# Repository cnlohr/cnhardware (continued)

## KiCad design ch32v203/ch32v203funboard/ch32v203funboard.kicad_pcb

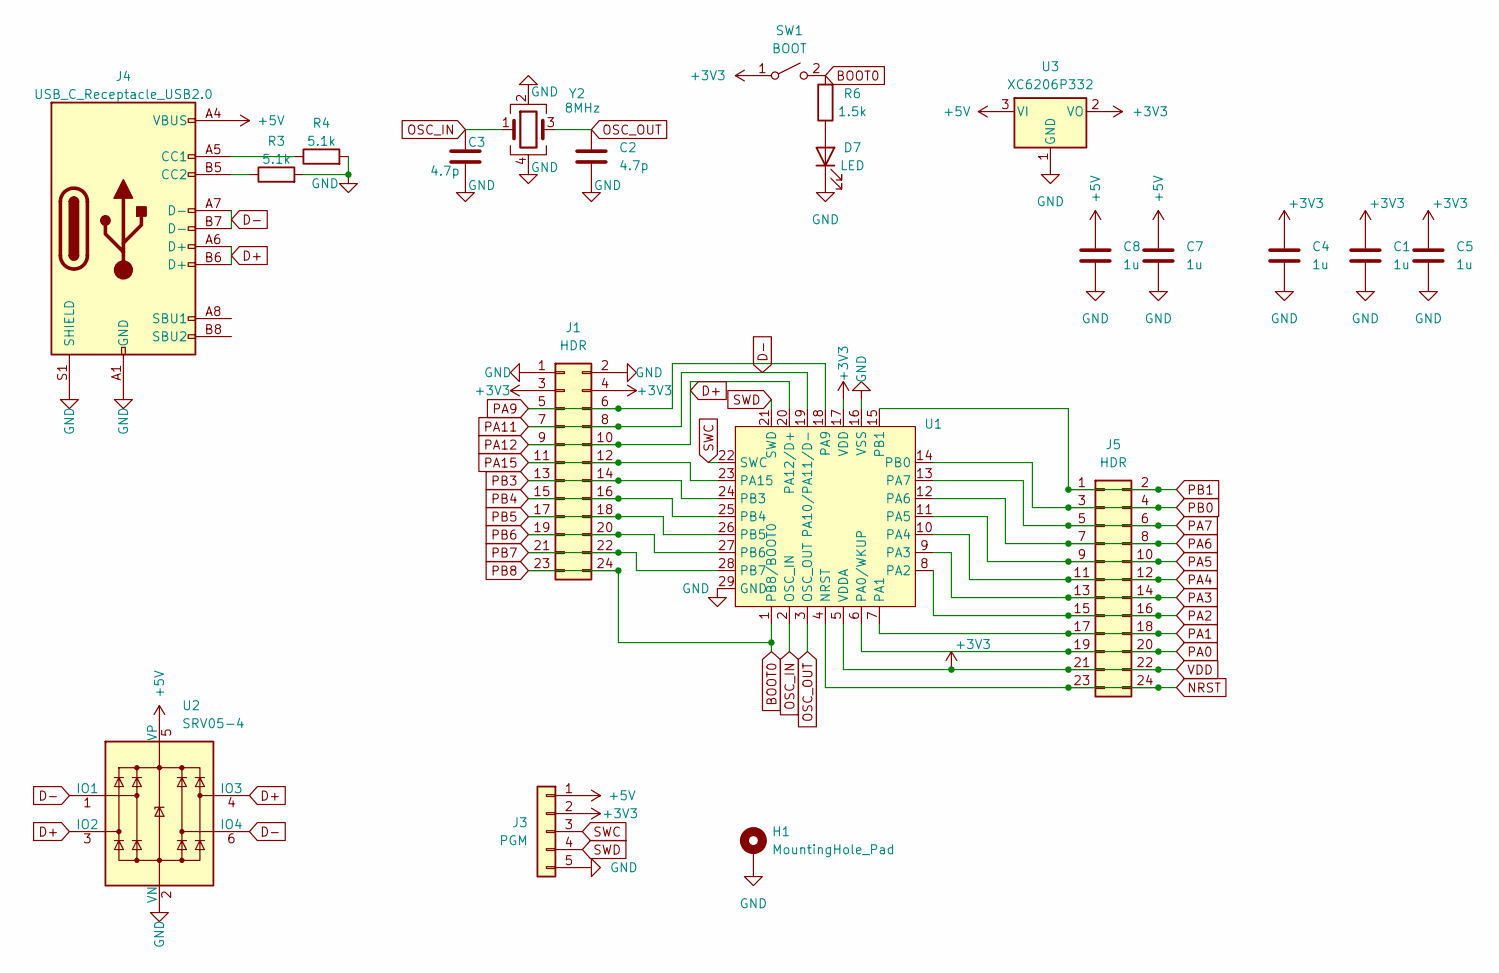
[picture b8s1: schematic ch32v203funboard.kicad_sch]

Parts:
C1, C4, C5, C7, C8: 1u; C_0402_1005Metric; LCSC C52923
C2, C3: 4.7p; C_0402_1005Metric; LCSC C325453
D7: LED; LED_0402_1005Metric; LCSC C74342
H1: MountingHole_Pad; MountingHole_3.2mm_M3_DIN965_Pad
J1, J5: HDR; PinHeader_2x12_P2.54mm_Vertical; LCSC C5383110
J3: PGM; PinHeader_1x05_P2.54mm_Vertical
J4: USB_C_Receptacle_USB2.0; USB_C_Receptacle_HRO_TYPE-C-31-M-12; LCSC C709358
R3, R4: 5.1k; R_0402_1005Metric; LCSC C25905
R6: 1.5k; R_0402_1005Metric; LCSC C25867
SW1: BOOT; TS-1187A-B-A-B-TACTILE; LCSC C318884
U1: QFN-28-1EP_4x4mm_P0.4mm_EP2.3x2.3mm; LCSC C5142280
U2: SRV05-4; SOT-23-6; LCSC C2836319
U3: XC6206P332; SOT-23; LCSC C5446
Y2: 8MHz; Crystal_SMD_3225-4Pin_3.2x2.5mm; LCSC C400090

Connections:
+5V: C7.1, C8.1, J3.1, J4.A4 (VBUS), J4.A9 (VBUS), J4.B4 (VBUS), J4.B9 (VBUS), U2.5 (VP), U3.3 (VI)
BOOT0: J1.23, J1.24, R6.2, SW1.2 (B), U1.1 (PB8/BOOT0)
D+: J1.9, J1.10, J4.A6 (D+), J4.B6 (D+), U1.20 (PA12/D+), U2.3 (IO2), U2.4 (IO3)
D-: J1.7, J1.8, J4.A7 (D-), J4.B7 (D-), U1.19 (PA10/PA11/D-), U2.1 (IO1), U2.6 (IO4)
GND: C1.2, C2.2, C3.2, C4.2, C5.2, C7.2, C8.2, D7.1 (K), H1.1, J1.1, J1.2, J3.5, J4.A1 (GND), J4.A12 (GND), J4.B1 (GND), J4.B12 (GND), J4.S1 (SHIELD), R3.2, R4.2, U1.16 (VSS), U1.29 (GND), U2.2 (VN), U3.1 (GND), Y2.2, Y2.4
NRST: J5.23, J5.24, U1.4 (NRST)
unnamed: D7.2 (A), R6.1
unnamed: J4.A5 (CC1), R4.1
unnamed: J4.B5 (CC2), R3.1
OSC_IN: C3.1, U1.2 (OSC_IN), Y2.1
OSC_OUT: C2.1, U1.3 (OSC_OUT), Y2.3
PA0: J5.19, J5.20, U1.6 (PA0/WKUP)
PA1: J5.17, J5.18, U1.7 (PA1)
PA2: J5.15, J5.16, U1.8 (PA2)
PA3: J5.13, J5.14, U1.9 (PA3)
PA4: J5.11, J5.12, U1.10 (PA4)
PA5: J5.9, J5.10, U1.11 (PA5)
PA6: J5.7, J5.8, U1.12 (PA6)
PA7: J5.5, J5.6, U1.13 (PA7)
PA9: J1.5, J1.6, U1.18 (PA9)
PA15: J1.11, J1.12, U1.23 (PA15)
PB0: J5.3, J5.4, U1.14 (PB0)
PB1: J5.1, J5.2, U1.15 (PB1)
PB3: J1.13, J1.14, U1.24 (PB3)
PB4: J1.15, J1.16, U1.25 (PB4)
PB5: J1.17, J1.18, U1.26 (PB5)
PB6: J1.19, J1.20, U1.27 (PB6)
PB7: J1.21, J1.22, U1.28 (PB7)
SWC: J3.3, U1.22 (SWC)
SWD: J3.4, U1.21 (SWD)
VDD: C1.1, C4.1, C5.1, J1.3, J1.4, J3.2, J5.21, J5.22, SW1.1 (A), U1.5 (VDDA), U1.17 (VDD), U3.2 (VO)

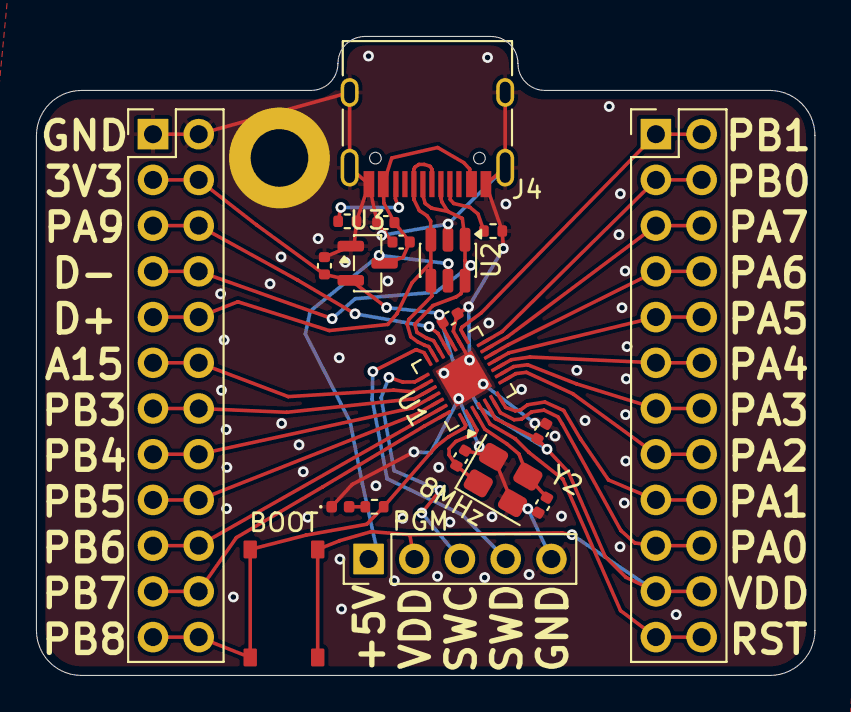
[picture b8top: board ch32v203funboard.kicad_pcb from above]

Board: 2 copper layers, 43.2 x 35.5 mm, 21 parts (0 on the bottom side), 31 nets.
